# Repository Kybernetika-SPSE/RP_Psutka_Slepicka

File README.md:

# Dílčí vypracovnání
[here](škola_info)
---

# 🛰️ Lokalizační systém na dvoupásovém vozidle pomocí ESP32, UWB a Wi-Fi

Tato ročníková práce představuje hybridní lokalizační systém postavený na platformě ESP32, který je integrován do dvoupásového robotického vozidla. Systém využívá **Ultra-Wideband (UWB)** pro přesné měření vzdáleností a **Wi-Fi fingerprinting** pro přibližnou lokalizaci. ESP32 zároveň umožňuje řízení vozidla nebo může fungovat jako samostatný **navigační modul** připojený přes Serial k jinému mikrokontroléru.

## ⚙️ Hlavní funkce

- 🚗 **Mobilní platforma:** ESP32 je umístěno na dvoupásovém vozidle a může jej samostatně ovládat.
- 🔁 **Modulární režim:** ESP32 lze přepnout do režimu **navigačního modulu** a komunikovat s jiným mikrokontrolérem přes sériovou linku.
- 📡 **UWB lokalizace:** Využívá se knihovna [`thotro/arduino-dw1000`](https://github.com/thotro/arduino-dw1000) pro přesné měření vzdáleností.
- 📶 **Wi-Fi fingerprinting:** ESP32 detekuje okolní Wi-Fi sítě a odhaduje polohu v neznámém prostředí.
- 🌐 **Webové rozhraní:** ESP32 hostuje jednoduchý web s informacemi o aktuální poloze.
- 🐍 **Python vizualizace:** V reálném čase je možné zobrazit pozici vozidla pomocí animace v Pythonu (`matplotlib`).
- 🔌 **Serial komunikace:** ESP32 odesílá výstupy polohy přes Serial — buď do počítače, nebo do jiného MCU.

## 📁 Struktura projektu

```
RP_Psutka_Slepicka/
├── PCB/                     # KiCad soubory pro návrh desky plošných spojů
├── modely/                  # 3D modely pro tisk
├── škola_info/              # Dílčí vypracování
├── docs/                    # Fotodokumentace
├── src/
│   ├── main/
│   │   ├── data/
│   │   │   ├── *.html       # Webové stránky hostované ESP32
│   │   │   └── *.json       # Hesla k Wi-Fi, uložené Wi-Fi fingerprinty
│   │   └── src/             # Zdrojový kód pro hlavní firmware ESP32
│   └── wifi-scan/           # ESP32 projekt pro sběr Wi-Fi fingerprintů
```

## 🧰 Použité technologie

- **ESP32-DevKitC v4**
- **DWM1000 UWB moduly**
- **PlatformIO + Arduino framework**
- **Python + matplotlib**
- **HTML + JavaScript (web na ESP32)**

## 🔧 Režimy provozu

### 🚘 Autonomní režim
ESP32 ovládá motorové jednotky vozidla a využívá lokalizaci pro navigaci.

### 🔗 Navigační modul
ESP32 funguje jako lokalizační jednotka připojená k jinému mikrokontroléru (např. další ESP32 nebo Arduino). Odhadovaná pozice je pravidelně posílána přes Serial.

## 💬 Komunikace po Serialu

Formát výstupu:
```
POS:[x,y] (2D) nebo POS:[x,y,z] (3D)
```

Možné rozšíření o příkazy pro změnu režimu, kalibraci, atd.

## 📸 Ukázky

## 📚 Zdroje

- [DW1000 datasheet](https://thetoolchain.com/mirror/dw1000/dw1000_user_manual_v2.05.pdf)
- [UWB localization – Wikipedia](https://en.wikipedia.org/wiki/Real-time_locating_system)
- [Arduino-DW1000 GitHub repo](https://github.com/thotro/arduino-dw1000)

## 📄 Licence

Projekt je vytvořen jako ročníková práce a není určen pro komerční použití.

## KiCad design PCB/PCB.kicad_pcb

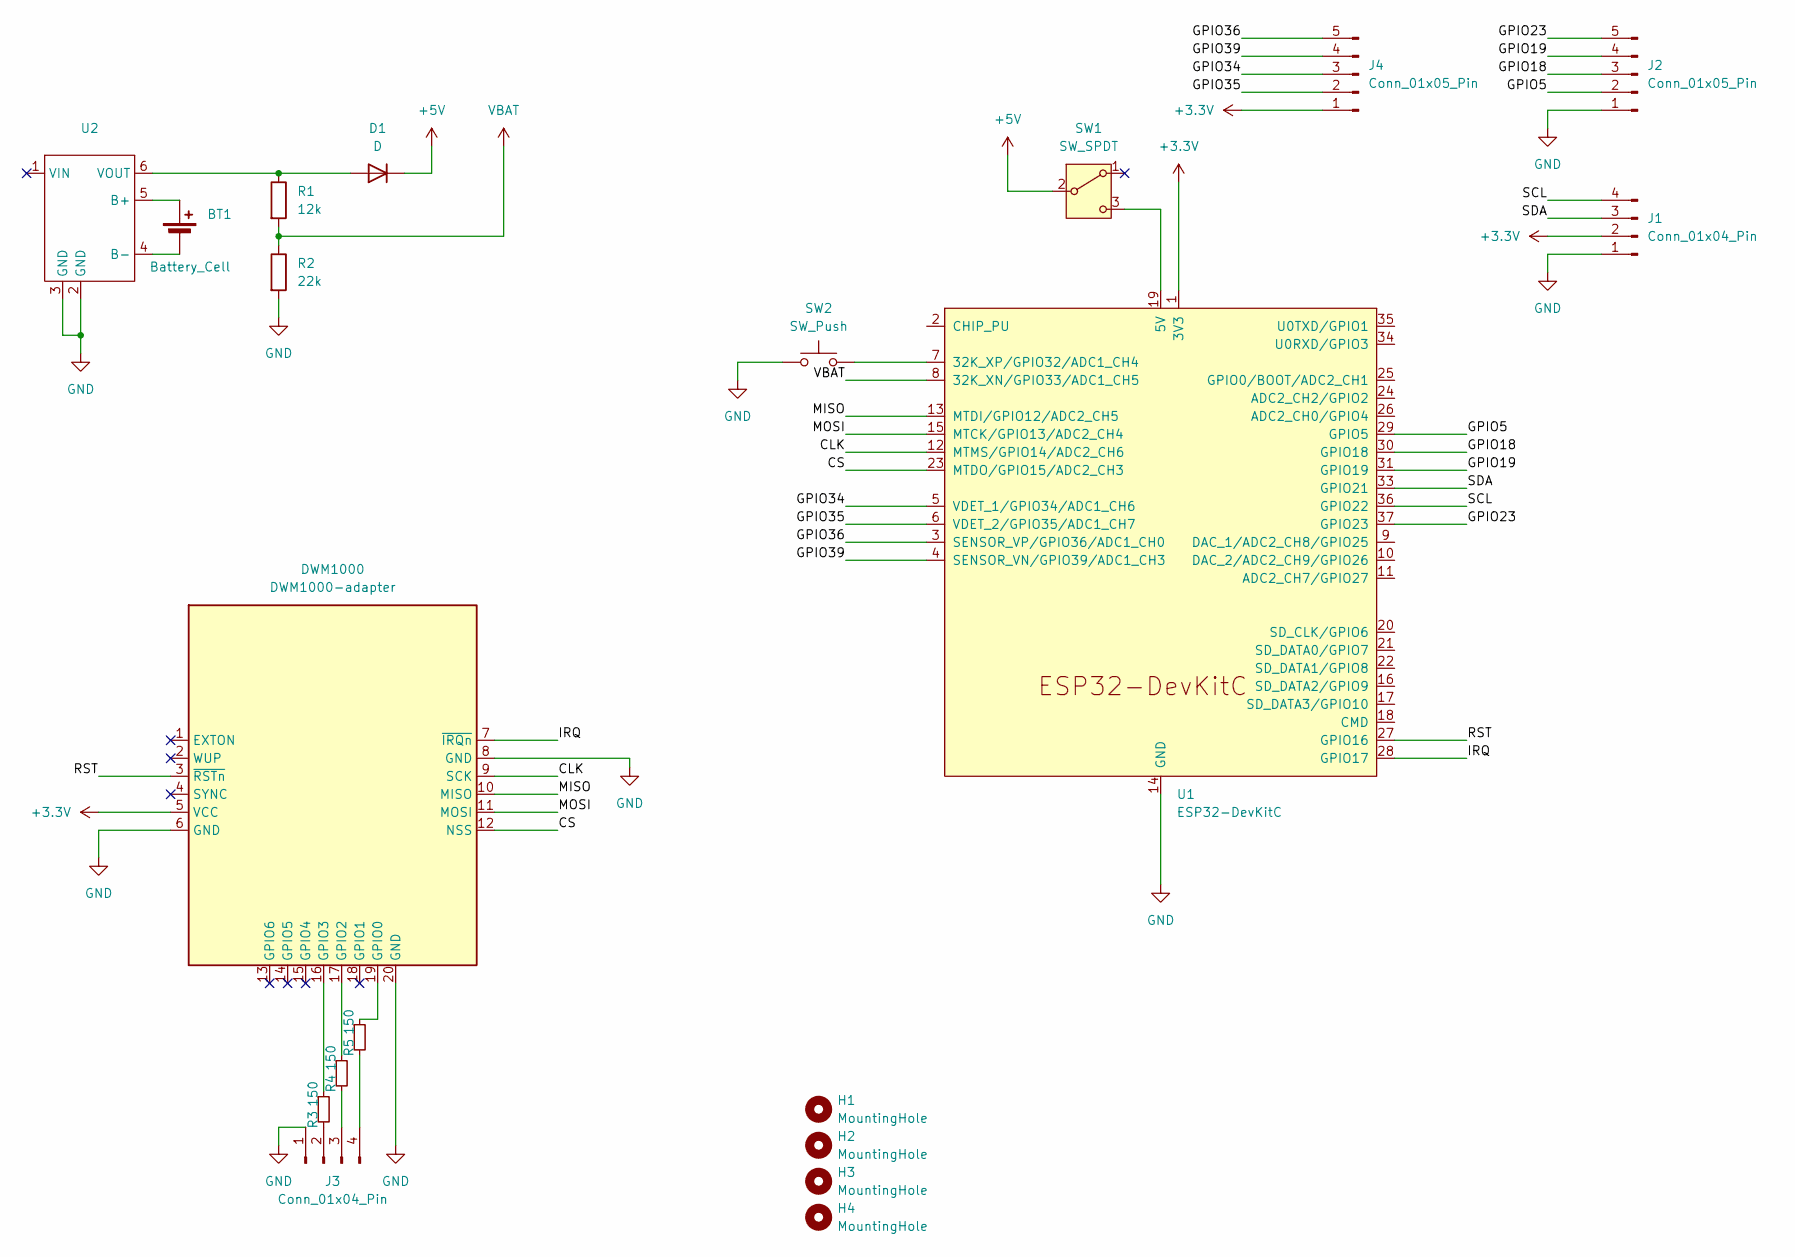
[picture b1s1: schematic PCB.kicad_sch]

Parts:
BT1: Battery_Cell; PinHeader_1x02_P2.54mm_Vertical
D1: D; D_A-405_P10.16mm_Horizontal
DWM1000: DWM1000-adapter; DWM1000 adapter
H1, H2, H3, H4: MountingHole; MountingHole_3.2mm_M3
J1, J3: Conn_01x04_Pin; PinHeader_1x04_P2.54mm_Vertical
J2, J4: Conn_01x05_Pin; PinHeader_1x05_P2.54mm_Vertical
R1: 12k; R_Axial_DIN0207_L6.3mm_D2.5mm_P10.16mm_Horizontal
R2: 22k; R_Axial_DIN0207_L6.3mm_D2.5mm_P10.16mm_Horizontal
R3, R4, R5: 150; R_0402_1005Metric
SW1: SW_SPDT; PinHeader_1x03_P2.54mm_Vertical
SW2: SW_Push; SW_PUSH-12mm
U1: ESP32-DevKitC
U2: TP4056-18650

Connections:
+3.3V: DWM1000.5 (VCC), J1.2, J4.1, U1.1 (3V3)
+5V: D1.1 (K), SW1.2 (B)
/CLK: DWM1000.9 (SCK), U1.12 (MTMS/GPIO14/ADC2_CH6)
/CS: DWM1000.12 (NSS), U1.23 (MTDO/GPIO15/ADC2_CH3)
/GPIO5: J2.2, U1.29 (GPIO5)
/GPIO18: J2.3, U1.30 (GPIO18)
/GPIO19: J2.4, U1.31 (GPIO19)
/GPIO23: J2.5, U1.37 (GPIO23)
/GPIO34: J4.3, U1.5 (VDET_1/GPIO34/ADC1_CH6)
/GPIO35: J4.2, U1.6 (VDET_2/GPIO35/ADC1_CH7)
/GPIO36: J4.5, U1.3 (SENSOR_VP/GPIO36/ADC1_CH0)
/GPIO39: J4.4, U1.4 (SENSOR_VN/GPIO39/ADC1_CH3)
/IRQ: DWM1000.7 (~IRQn), U1.28 (GPIO17)
/MISO: DWM1000.10 (MISO), U1.13 (MTDI/GPIO12/ADC2_CH5)
/MOSI: DWM1000.11 (MOSI), U1.15 (MTCK/GPIO13/ADC2_CH4)
/RST: DWM1000.3 (~RSTn), U1.27 (GPIO16)
/SCL: J1.4, U1.36 (GPIO22)
/SDA: J1.3, U1.33 (GPIO21)
GND: DWM1000.6 (GND), DWM1000.8 (GND), DWM1000.20 (GND), J1.1, J2.1, J3.1, R2.2, SW2.1, U1.14 (GND), U1.32 (GND), U1.38 (GND), U2.2 (GND), U2.3 (GND)
unnamed: BT1.1 (+), U2.5 (B+)
unnamed: BT1.2 (-), U2.4 (B-)
unnamed: D1.2 (A), R1.1, U2.6 (VOUT)
unnamed: DWM1000.19 (GPIO0), R5.1
unnamed: DWM1000.17 (GPIO2), R4.1
unnamed: DWM1000.16 (GPIO3), R3.1
unnamed: J3.2, R3.2
unnamed: J3.3, R4.2
unnamed: J3.4, R5.2
unnamed: SW1.3 (C), U1.19 (5V)
unnamed: SW2.2, U1.7 (32K_XP/GPIO32/ADC1_CH4)
VBAT: R1.2, R2.1, U1.8 (32K_XN/GPIO33/ADC1_CH5)

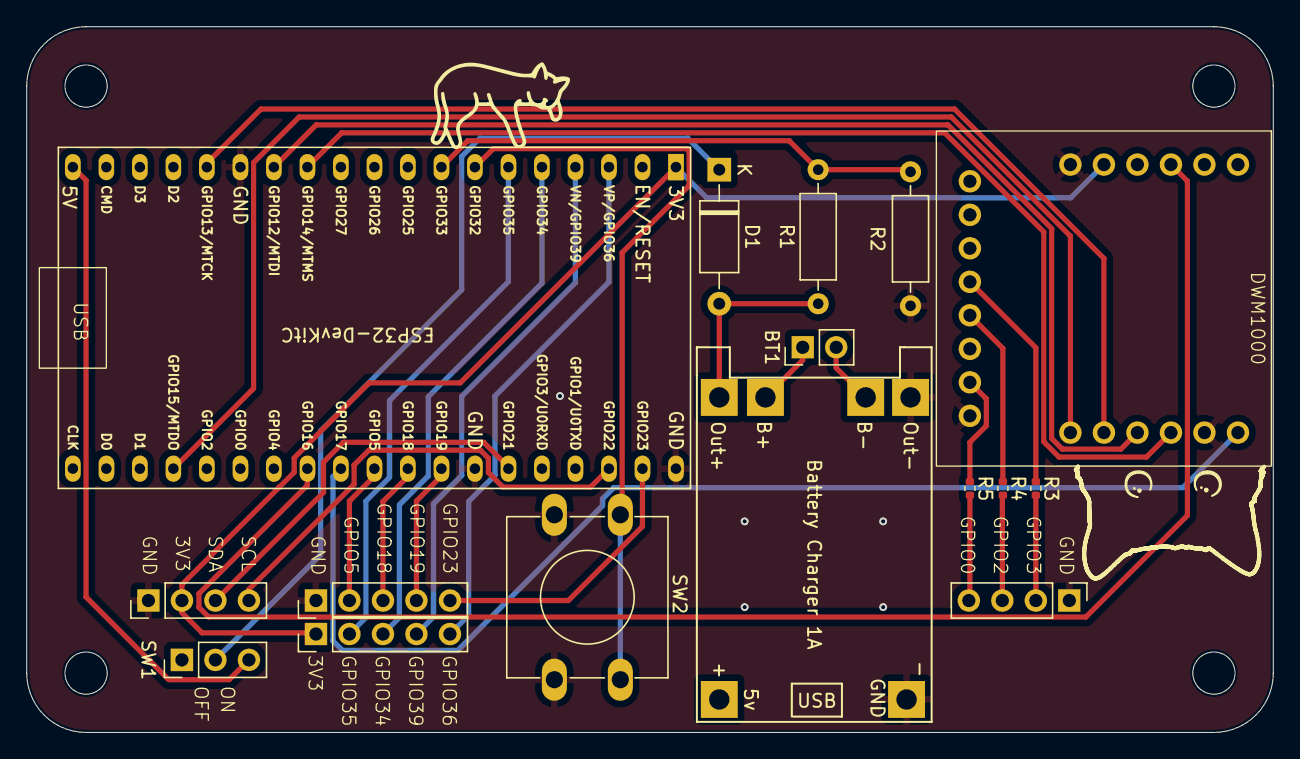
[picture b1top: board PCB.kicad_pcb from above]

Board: 2 copper layers, 94.5 x 53.5 mm, 20 parts (0 on the bottom side), 31 nets.

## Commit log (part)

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2024-11-26 fixed corrupted pdf
2024-11-26 better README
2024-11-26 Moje zadání verze 0.1
2024-11-27 zadání verze 1.0
2024-11-27 zadání verze 1.1
2024-11-29 zadání verze 1.2
2024-12-03 test git
2024-12-19 restructer of the repo
2024-12-19 restructure of the repo 2
2024-12-19 adding report to date 20.12.2024
2024-12-27 TODO list update
2024-12-27 slightly edited ESP-IDF example on WiFi-scan
2024-12-27 progress to TODO list
2024-12-27 scan "functional"
2024-12-27 saving readable logs
2025-01-07 Report update
2025-01-07 report repair
2025-01-07 report
2025-01-17 ading .gitignore to save me from headache
2025-01-17 scan files upload
2025-01-17 ESP-IDF example for reading pins
2025-01-17 ESP-IDF Simple HTTPD Server Example
2025-01-17 removed school_project from this branch
2025-01-18 cleaning
2025-01-18 PCB schematic (WIP)
2025-01-18 cleanup
2025-01-18 PCB progress
2025-01-19 PCB is finished, but esp is the wrong way :(
2025-01-19 PCB redesign
2025-01-19 kočky :D
2025-01-21 PCB update
2025-01-24 repaired the size of an esp
2025-01-29 rewrote wifi-scan from C to arduino
2025-01-29 upgraded save_to_file.py that now saves to .csv files instead
2025-01-29 README update
2025-01-30 updated .gitignore for wifi-scan
2025-01-30 example for UWB anchor and tag
2025-01-31 added model folder, renamed school_project
2025-01-31 added report for this month
2025-01-31 reformated dates in the names of reports
2025-02-04 address is now a variable
2025-02-05 merged code for tag and anchor to a single file
2025-02-05 added some basic control and status page controling onboard LED
2025-02-09 status page code update
2025-02-09 testing out SPIFFS for file system
2025-02-09 added auto_connect_to_wifi for better user expirience
2025-02-11 testing access point
2025-02-13 deleted old WiFi scan as there will be no more use for it
2025-02-13 adding some helpful functionalities for conneting to a WiFi network
2025-02-13 renamed file_system to main and moved all files a step up from locator to src
2025-02-15 rewrited main.cpp for better usage and readability
2025-02-15 seperated out LED_test to its own file
2025-02-15 quick fix
2025-02-16 added scan wifi function into a utils
2025-02-16 fix the scan_wifi function
2025-02-17 added connect_to_wifi function + rewrited for better readability
2025-02-18 start_AP function for starting access piont
2025-02-18 renamed škola info folder
2025-02-18 added report
2025-02-18 fixed README.md
2025-02-19 wifi_connection mode
2025-02-19 added pins for motor encoders
2025-02-19 deleting status pag. It's all written in main under LED_test now.
2025-02-19 Deleted simple, beacause I am using a differnt system now so there is no need for it.
2025-02-19 Deleting generic_gpio. No use for it
2025-02-22 added ability to send strings in LED_test
2025-02-22 fix: correct RSSI value handling in WiFi scanning
2025-02-22 now it is much easier to scan networks and save them to .json file automaticly
2025-02-23 data formatting to JSON for reading by ESP
2025-02-23 refactor: move JSON files to scanData directory and update paths in scripts
2025-02-23 cleanup: remove unused directories and .travis.yml files from wifi-scan directory
2025-02-23 renamed WiFiScan for consitnecy and cleand up platfomio.ini
2025-02-23 docs: update README files for wifi-scan and scanData with usage instructions and file structure
2025-02-25 new wifi connection website
2025-02-25 new header for encoders, adjusted resitor values
2025-02-25 new models with holes for pogo pins
2025-02-25 created main menu for website
2025-02-25 updated control menu
2025-02-25 docs: update README.md in scanData to clarify data structure and file contents
2025-02-25 cleanup: add .gitignore for scanData and remove obsolete JSON files
2025-02-25 feat: implement WiFi location matching functionality with similarity calculation
2025-02-26 better button animations
2025-02-26 renamed main.html to index.html
2025-02-26 cleanup: remove obsolete files from UWB directories
2025-02-27 fix: fixed wrong wiring of the UWB
2025-02-28 added holes for pins to models
2025-02-28 Add files via upload
    new report
2025-02-28 upload report
2025-03-05 refactor: modularize data processing functions for loading, grouping, and saving WiFi scan data
2025-03-05 refactor: enhance Wi-Fi scanning functionality with LED feedback and modularize scanning process
2025-03-05 feat: add UWB module with setup and loop functions for device ranging
2025-03-05 refactor: update platformio.ini to support multiple ESP32 environments with distinct upload and monitor ports and modes for UWB
2025-03-05 refactor: some minor changes docs: add comments to the code
2025-03-05 feat: implement Wi-Fi connection handling with dynamic network fetching
2025-03-06 feat: implement location handling with HTTP endpoints for Wi-Fi scanning and matching
2025-03-06 chore: remove unused include and lib directories
2025-03-06 refactor: update JSON handling in Wi-Fi location module and adjust route definitions
2025-03-06 refactor: simplify JSON handling for Wi-Fi credentials in connection logic
2025-03-12 new project for creating tracing logic
2025-03-12 feat: add matrix class with multiplication and print functionality
2025-03-14 renamed to matrix.cpp and added some new functions into the Matrix class
2025-03-14 feat: implement matrix inversion with error handling for non-square and singular matrices
2025-03-14 feat: implement Kalman Filter class for state estimation and prediction
2025-03-14 fix: add missing semicolon in KalmanFilter::getState method
2025-03-15 feat: update set_identity method to include scaling factor
2025-03-15 fix: update inverse method to return empty matrix for non-square and singular matrices
2025-03-15 feat: implement QR decomposition method in Matrix class
2025-03-15 fix: add const qualifier to qrDecomposition method in Matrix class
2025-03-15 feat: implement least squares solver using QR decomposition
2025-03-23 IT WOOOOOORKSSSSS
2025-03-23 refactor: remove debug print statements from solveLeastSquares function
2025-03-23 refactor: improve code readability and documentation in least squares and Kalman filter implementations
2025-03-25 refactor: remove debug print statements from qrDecomposition method in Matrix class
2025-03-26 feat: add QR decomposition-based matrix inversion method and rename existing inverse method
2025-03-26 refactor: simplify solveLeastSquares function by using inverse of R for solution
2025-03-27 refactor: add rows and cols methods to Matrix class for improved dimension handling
2025-03-27 feat: add getColumn method to Matrix class for column extraction
2025-03-28 feat: add norm method to Matrix class for Euclidean norm computation
2025-03-28 feat: implement Singular Value Decomposition (SVD) using Jacobi method
2025-03-28 feat: add computeEquations function for least squares problem formulation
2025-03-28 separate css file
2025-03-28 feat: enhance Matrix class with error handling and some cleanup
2025-03-28 feat: improve error handling in Matrix class by returning appropriate fallback matrices
2025-03-28 progress report
2025-03-28 feat: update KalmanFilter to support variable dimensions and enhance state management
2025-03-28 feat: enhance error messages in Matrix class for dimension mismatch in addition and subtraction
2025-03-28 feat: add computeCentroid function to calculate the centroid of a set of coordinates with error handling for empty matrices
2025-03-28 feat: add isCoplanar function to check coplanarity of points based on singular values
2025-03-29 feat: add findPlane function to derive plane equation from SVD results
2025-03-29 feat: add projectPointsOntoPlane function to project points onto a defined plane
2025-03-29 feat: add documentation for projectPointsOntoPlane
2025-03-29 feat: add convert3DTo2D function to project 3D points onto a plane using basis vectors
2025-03-29 fix: correct normal vector assignment in findPlane function
2025-03-29 feat: add isCollinear function to check if 3D points are collinear using cross product
2025-03-29 fix: improve error messages in solveLeastSquares function for better clarity
2025-03-30 feat: add reconstruct3D function to convert 2D coordinates back to 3D using plane basis vectors
2025-03-30 fix: enhance input validation in reconstruct3D function for better error handling
2025-03-30 refactor: simplify reconstruct3D function by removing unnecessary centroid parameter
2025-03-30 fix: remove unnecessary centroid validation from reconstruct3D function
2025-03-30 refactor: change the the size of the LS result from 3x1 to 1x3
2025-03-31 Fix: fixed README links and added new ones
2025-04-01 feat: implement trilateration class with initialization and data point update methods
2025-04-03 feat: refactor trilateration class to include constructor and state retrieval method
2025-04-03 feat: add printBuffer method to display buffer contents in trilateration class
2025-04-05 feat: add default constructor for Matrix class to initialize an empty matrix
2025-04-05 feat: add eigen decomposition method to Matrix class for symmetric matrices
2025-04-05 feat: overload * operator to multiply a matrix by a scalar
2025-04-05 feat: add setColumn method to Matrix class for setting column values
2025-04-06 refactor: remove eigen decomposition method from Matrix class
2025-04-06 fix: SVD now actually works
2025-04-06 feat: implement trilateration logic and update serial input handling
2025-04-10 refactor: renamed the reports
2025-04-12 docs: update README with project details and add new images
2025-04-17 feat: UWB finally works, meassures distances, runtime mode switch
2025-04-17 fix: swap UWB_PIN_SPI_IRQ and UWB_PIN_SPI_RST definitions for correct pin mapping
2025-04-17 docs: add comments to the UWB functions
2025-04-17 feat: add UWB Control Panel HTML interface for managing ranging and mode switching
2025-04-17 feat: add HTML endpoints for LED test, Wi-Fi connection, and location handling
2025-04-18 feat: implement averaging for distance measurements in UWB module
2025-04-18 feat: add UWB calibration functionality
2025-04-18 feat: add calibration feature to UWB Control Panel HTML interface
2025-04-18 fix: correct password key in Wi-Fi credential handling
2025-04-18 refactor: renamed place.html to location.html
2025-04-18 fix: adjust delay parameters and improve calibration logging in UWB module
2025-04-20 fixed index
2025-04-20 actually fixed index
2025-04-20 add css to UWB website
2025-04-21 feat: implement preferences for antenna delay and ranging state management
2025-04-22 tweak
2025-04-22 Added schematic for the car
2025-04-22 Updated models
2025-04-22 better progress report
2025-04-28 my documentation
2025-04-30 feat: enhance trilateration logic to support dynamic 2D/3D mode switching
2025-04-30 feat: add UWB simulation logic with ESP32 communication and animation
2025-04-30 fix: update window.onload to fetch WiFi networks instead of rendering fixed list
2025-04-30 refactor: reorganize code structure and enhance WiFi handling with new routing and error handling
2025-04-30 refactor: improve code readability by adding comments to main function and entry point
2025-04-30 feat: add credential configuration file for WiFi SSID and password example
2025-04-30 feat: implement serial input handling
2025-04-30 feat: add UWB start and stop functions, rename switchMode for clarity
2025-04-30 feat: moved the trilateration logic into the main project
2025-04-30 fix: fixed UWB functions to their new names and reduce redundancy
2025-04-30 feat: add PCB design document
2025-04-30 feat: add documentation
2025-07-02 feat: enabled inputing multiple points at the same times and deleted uneccessary Serial prints
2025-07-04 feat: add printJSON method to output matrix in JSON format
2025-07-04 feat: add JSON output for trilateration solution and Kalman filter state
2025-07-19 fix: PCA algorithm now works and is separeted into two functions
2025-07-20 feat: enhance eigenJacobi method to sort eigenvalues and eigenvectors by absolute value
